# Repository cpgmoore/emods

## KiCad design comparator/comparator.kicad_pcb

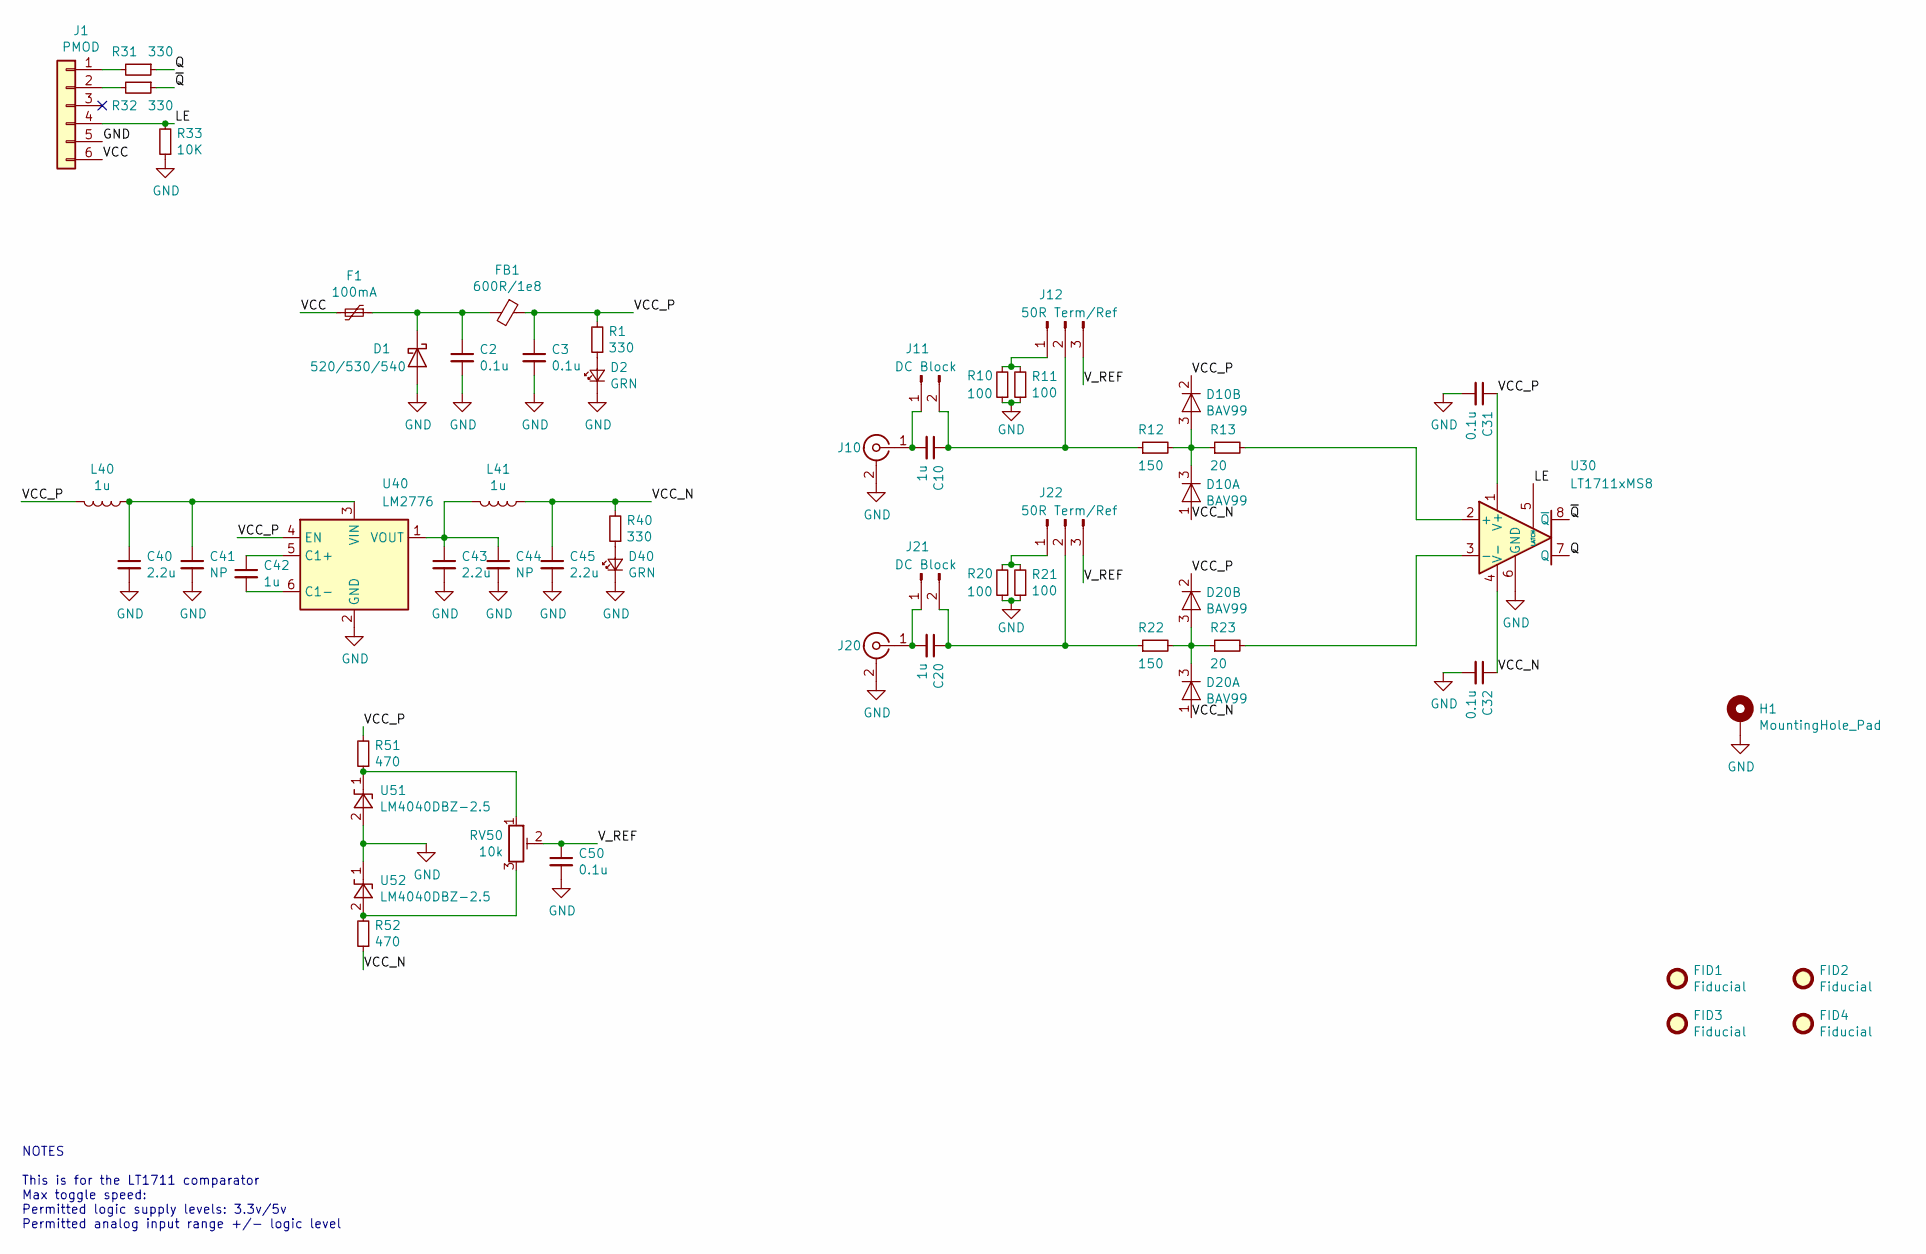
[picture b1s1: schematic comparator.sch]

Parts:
C2, C3, C31, C32, C50: 0.1u; C_0603_1608Metric
C10, C20, C42: 1u; C_0603_1608Metric
C40, C43, C45: 2.2u; C_0603_1608Metric
C41, C44: NP; C_0603_1608Metric
D1: 520/530/540; D_SOD-123
D2, D40: GRN; LED_0603_1608Metric
D10, D20: BAV99; SOT-23
F1: 100mA; Fuse_1206_3216Metric
FB1: 600R/1e8; L_0603_1608Metric
FID1, FID2, FID3, FID4: Fiducial; Fiducial_1mm_Mask2mm
H1: MountingHole_Pad; MountingHole_3.5mm_Pad_Via
J1: PMOD; PinHeader_1x06_P2.54mm_Vertical
J10, J20: SMA; SMA_Samtec_SMA-J-P-H-ST-EM1_EdgeMount
J11, J21: DC Block; PinHeader_1x02_P2.54mm_Vertical
J12, J22: 50R Term/Ref; PinHeader_1x03_P2.54mm_Vertical
L40, L41: 1u; L_0603_1608Metric
R1, R31, R32, R40: 330; R_0603_1608Metric
R10, R11, R20, R21: 100; R_0603_1608Metric
R12, R22: 150; R_0603_1608Metric
R13, R23: 20; R_0603_1608Metric
R33: 10K; R_0603_1608Metric
R51, R52: 470; R_0603_1608Metric
RV50: 10k; Potentiometer_Bourns_3299W_Vertical
U30: LT1711xMS8; MSOP-8_3x3mm_P0.65mm
U40: LM2776; SOT-23-6
U51, U52: LM4040DBZ-2.5; SOT-23

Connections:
/LE: J1.4, R33.2, U30.5 (LATCH)
/Q: R31.1, U30.7 (Q)
/VCC: F1.2, J1.6
/VCC_N: C32.1, C45.1, D10.1 (A), D20.1 (A), L41.1, R40.2, R52.1, U30.4 (V-)
/VCC_P: C3.1, C31.1, D10.2 (K), D20.2 (K), FB1.1, L40.2, R1.2, R51.2, U30.1 (V+), U40.4 (EN)
/V_REF: C50.1, J12.3, J22.3, RV50.2
/~Q: R32.1, U30.8 (~Q)
GND: C2.2, C3.2, C31.2, C32.2, C40.2, C41.2, C43.2, C44.2, C45.2, C50.2, D1.2 (A), D2.1 (K), D40.1 (K), H1.1, J1.5, J10.2 (Ext), J20.2 (Ext), R10.1, R11.1, R20.1, R21.1, R33.1, U30.6 (GND), U40.2 (GND), U51.2 (A), U52.1 (K)
unnamed: C2.1, D1.1 (K), F1.1, FB1.2
unnamed: C10.1, J11.2, J12.2, R12.1
unnamed: C10.2, J10.1 (In), J11.1
unnamed: C20.1, J21.2, J22.2, R22.1
unnamed: C20.2, J20.1 (In), J21.1
unnamed: C40.1, C41.1, L40.1, U40.3 (VIN)
unnamed: C42.1, U40.5 (C1+)
unnamed: C42.2, U40.6 (C1-)
unnamed: C43.1, C44.1, L41.2, U40.1 (VOUT)
unnamed: D2.2 (A), R1.1
unnamed: D10.3 (K), R12.2, R13.1
unnamed: D20.3 (K), R22.2, R23.1
unnamed: D40.2 (A), R40.1
unnamed: J1.1, R31.2
unnamed: J1.2, R32.2
unnamed: J12.1, R10.2, R11.2
unnamed: J22.1, R20.2, R21.2
unnamed: R13.2, U30.2 (+)
unnamed: R23.2, U30.3 (-)
unnamed: R51.1, RV50.1, U51.1 (K)
unnamed: R52.2, RV50.3, U52.2 (A)

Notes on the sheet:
NOTES This is for the LT1711 comparator Max toggle speed: Permitted logic supply levels: 3.3v/5v Permitted analog input range +/- logic level

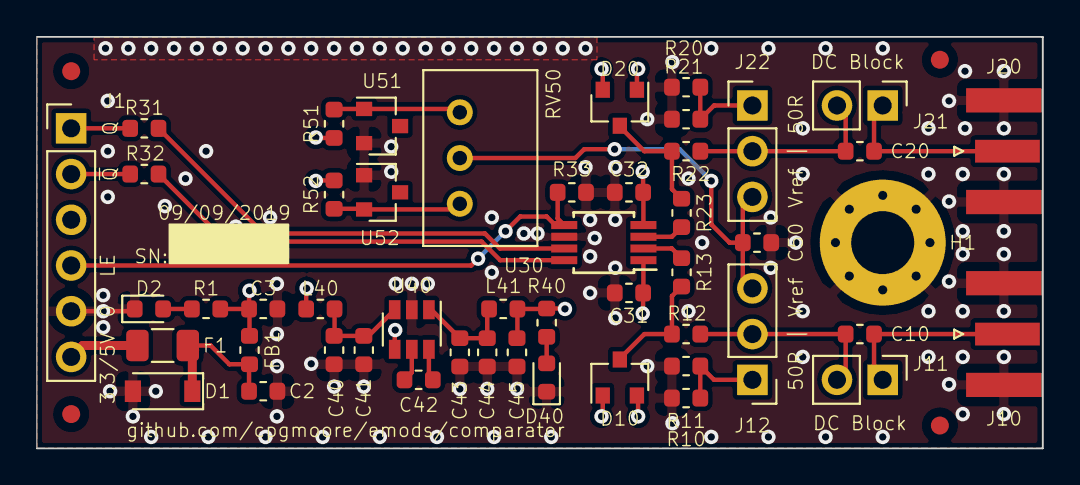
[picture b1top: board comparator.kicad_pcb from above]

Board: 4 copper layers, 55.9 x 22.9 mm, 54 parts (0 on the bottom side), 29 nets.

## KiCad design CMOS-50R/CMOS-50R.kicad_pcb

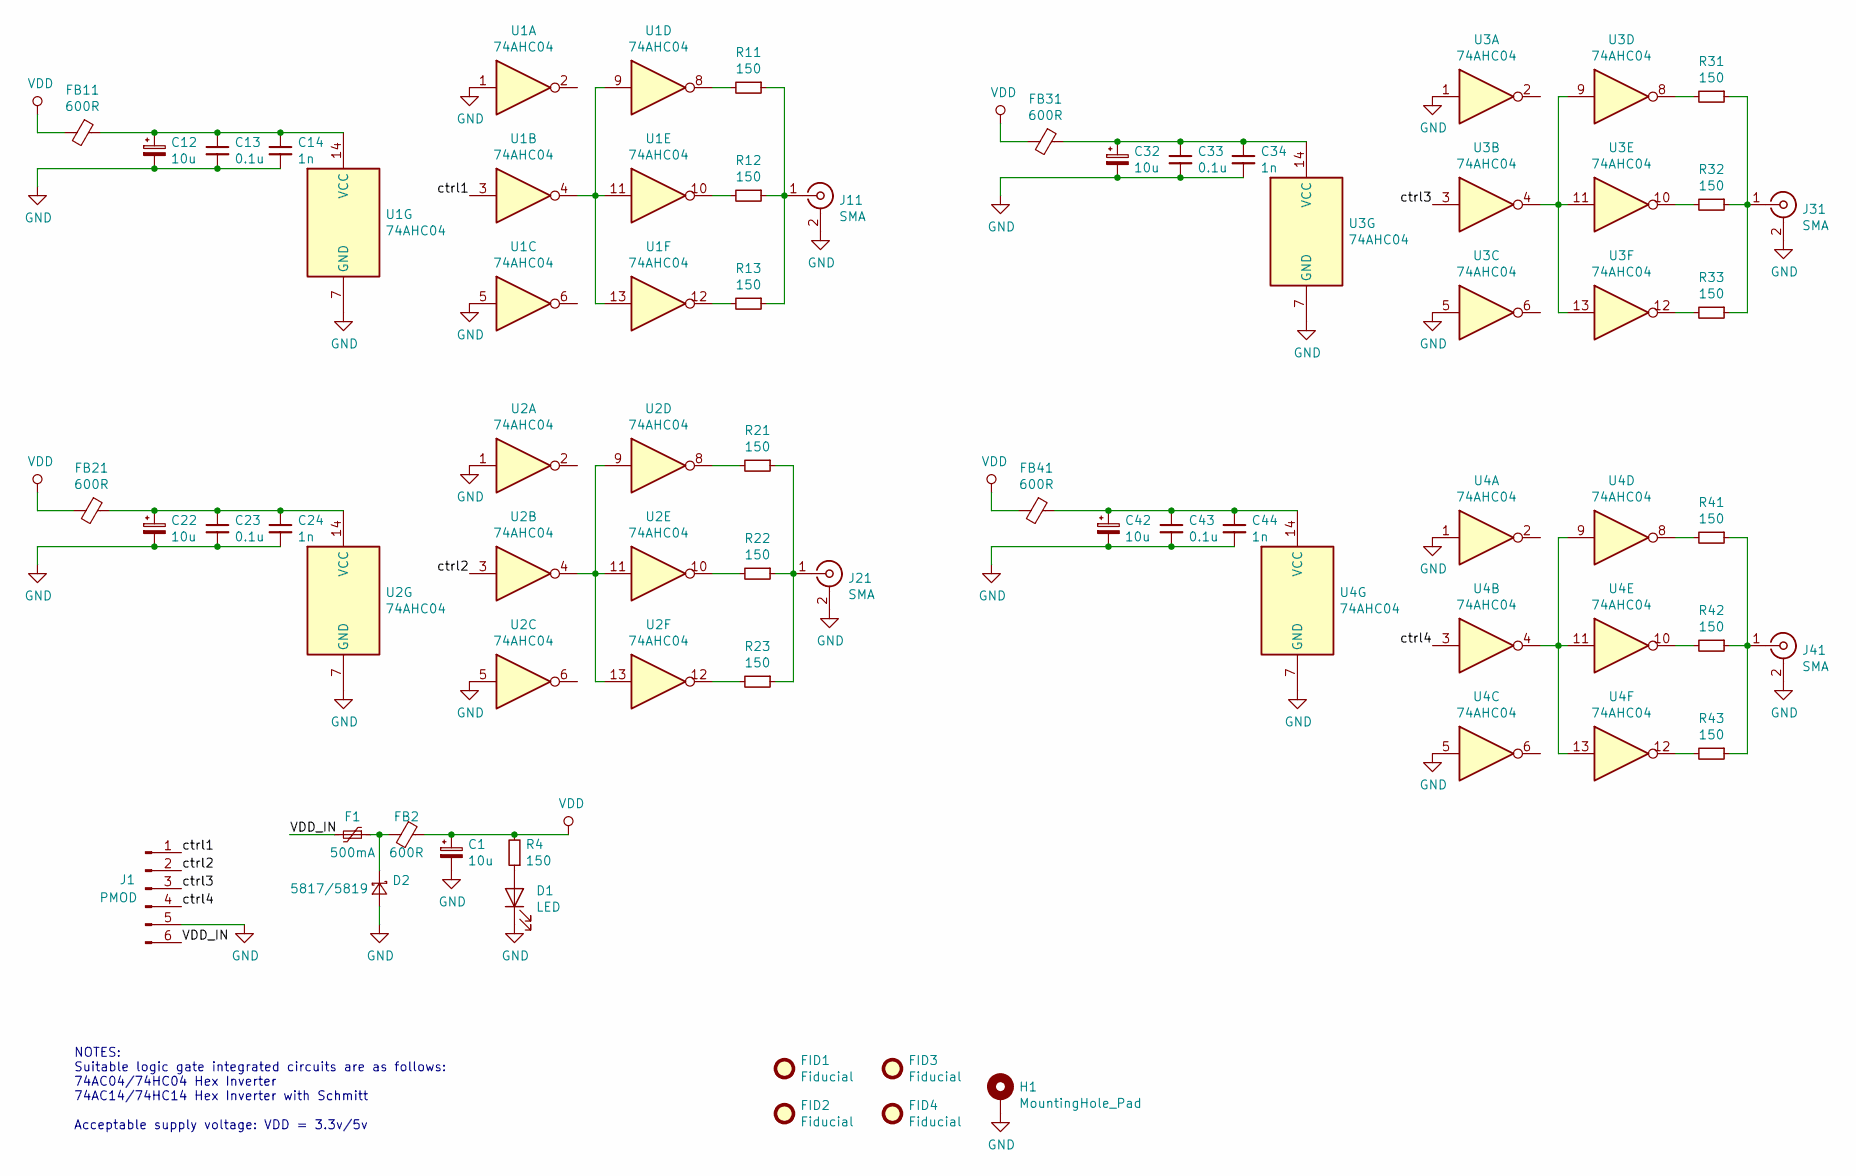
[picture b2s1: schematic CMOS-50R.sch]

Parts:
C1, C12, C22, C32, C42: 10u; CP_EIA-2012-12_Kemet-R
C13, C23, C33, C43: 0.1u; C_0603_1608Metric
C14, C24, C34, C44: 1n; C_0603_1608Metric
D1: LED; LED_0805_2012Metric
D2: 5817/5819; D_SOD-123
F1: 500mA; Fuse_1206_3216Metric
FB2, FB11, FB21, FB31, FB41: 600R; L_0603_1608Metric
FID1, FID2, FID3, FID4: Fiducial; Fiducial_1mm_Mask2mm
H1: MountingHole_Pad; MountingHole_3.5mm_Pad_Via
J1: PMOD; PinHeader_1x06_P2.54mm_Vertical
J11, J21, J31, J41: SMA; SMA_Amphenol_132134-11_Vertical
R4, R11, R12, R13, R21, R22, R23, R31, R32, R33, R41, R42, R43: 150; R_0805_2012Metric
U1, U2, U3, U4: 74AHC04; SOIC-14_3.9x8.7mm_P1.27mm

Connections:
/VDD_IN: F1.2, J1.6
/ctrl1: J1.1, U1.3
/ctrl2: J1.2, U2.3
/ctrl3: J1.3, U3.3
/ctrl4: J1.4, U4.3
GND: C1.2, C12.2, C13.2, C14.2, C22.2, C23.2, C24.2, C32.2, C33.2, C34.2, C42.2, C43.2, C44.2, D1.1 (K), D2.2 (A), H1.1, J1.5, J11.2 (Ext), J21.2 (Ext), J31.2 (Ext), J41.2 (Ext), U1.1, U1.5, U1.7 (GND), U2.1, U2.5, U2.7 (GND), U3.1, U3.5, U3.7 (GND), U4.1, U4.5, U4.7 (GND)
unnamed: C12.1, C13.1, C14.1, FB11.1, U1.14 (VCC)
unnamed: C22.1, C23.1, C24.1, FB21.1, U2.14 (VCC)
unnamed: C32.1, C33.1, C34.1, FB31.1, U3.14 (VCC)
unnamed: C42.1, C43.1, C44.1, FB41.1, U4.14 (VCC)
unnamed: D1.2 (A), R4.1
unnamed: D2.1 (K), F1.1, FB2.2
unnamed: J11.1 (In), R11.1, R12.1, R13.1
unnamed: J21.1 (In), R21.1, R22.1, R23.1
unnamed: J31.1 (In), R31.1, R32.1, R33.1
unnamed: J41.1 (In), R41.1, R42.1, R43.1
unnamed: R11.2, U1.8
unnamed: R12.2, U1.10
unnamed: R13.2, U1.12
unnamed: R21.2, U2.8
unnamed: R22.2, U2.10
unnamed: R23.2, U2.12
unnamed: R31.2, U3.8
unnamed: R32.2, U3.10
unnamed: R33.2, U3.12
unnamed: R41.2, U4.8
unnamed: R42.2, U4.10
unnamed: R43.2, U4.12
unnamed: U1.4, U1.9, U1.11, U1.13
unnamed: U2.4, U2.9, U2.11, U2.13
unnamed: U3.4, U3.9, U3.11, U3.13
unnamed: U4.4, U4.9, U4.11, U4.13
VDD: C1.1, FB2.1, FB11.2, FB21.2, FB31.2, FB41.2, R4.2

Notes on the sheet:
NOTES: Suitable logic gate integrated circuits are as follows: 74AC04/74HC04 Hex Inverter 74AC14/74HC14 Hex Inverter with Schmitt Acceptable supply voltage: VDD = 3.3v/5v

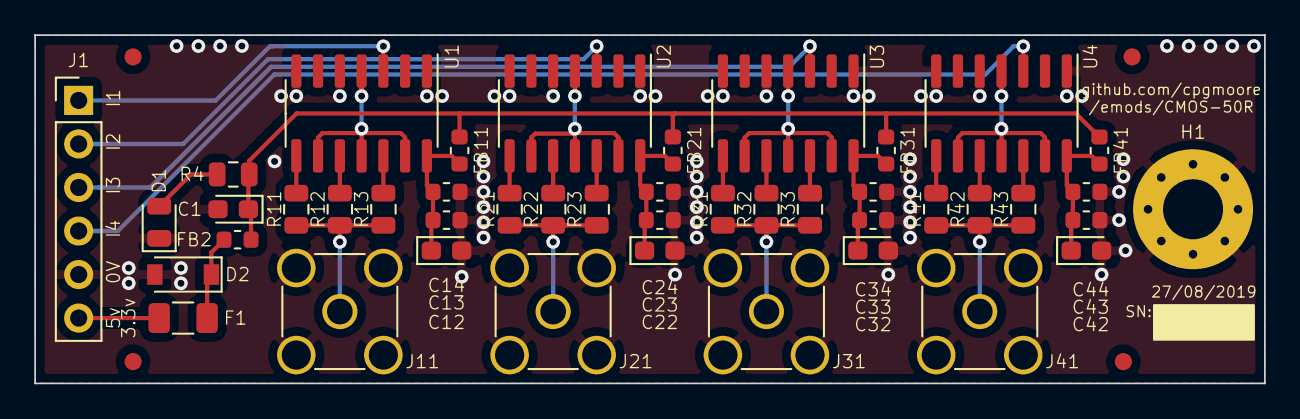
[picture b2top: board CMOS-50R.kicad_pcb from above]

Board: 2 copper layers, 71.8 x 20.3 mm, 48 parts (0 on the bottom side), 33 nets.

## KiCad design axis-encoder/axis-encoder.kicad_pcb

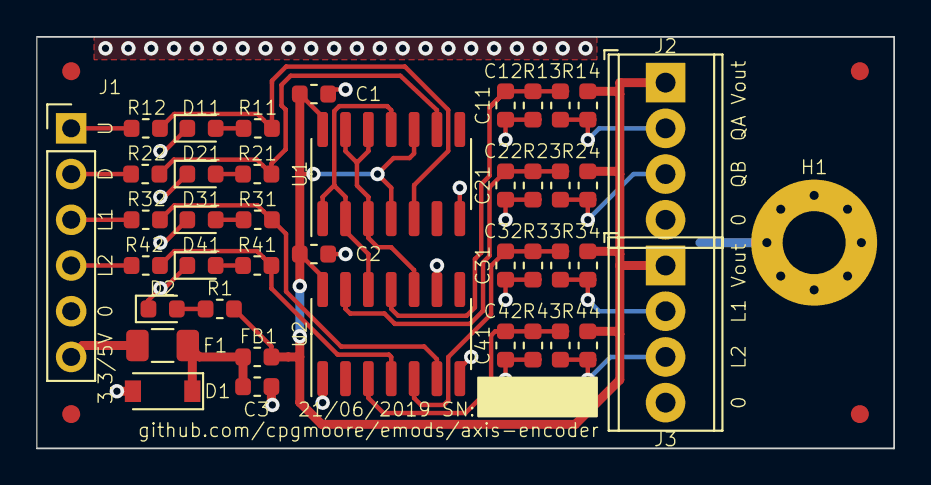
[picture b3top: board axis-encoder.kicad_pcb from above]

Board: 2 copper layers, 47.6 x 22.9 mm, 46 parts (0 on the bottom side), 27 nets.

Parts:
C1, C2, C3: 0.1u; C_0603_1608Metric
C11, C21, C31, C41: 1n; C_0603_1608Metric
C12, C22, C32, C42: NP; C_0603_1608Metric
D1: 520/530/540; D_SOD-123
D2: GRN; LED_0603_1608Metric
D11, D21, D31, D41: RED; LED_0603_1608Metric
F1: 100mA; Fuse_1206_3216Metric
FB1: 600R/1e8; L_0603_1608Metric
FID1, FID2, FID3, FID4: Fiducial; Fiducial_1mm_Mask2mm
H1: MountingHole_Pad; MountingHole_3.5mm_Pad_Via
J1: PMOD; PinHeader_1x06_P2.54mm_Vertical
J2: Encoder; TerminalBlock_Phoenix_MPT-0,5-4-2.54_1x04_P2.54mm_Horizontal
J3: Limits; TerminalBlock_Phoenix_MPT-0,5-4-2.54_1x04_P2.54mm_Horizontal
R1, R11, R21, R31, R41: 330; R_0603_1608Metric
R12, R14, R22, R24, R32, R34, R42, R44: 1k; R_0603_1608Metric
R13, R23, R33, R43: 10k; R_0603_1608Metric
U1: 74xx74; SOIC-14_3.9x8.7mm_P1.27mm
U2: 74xx14; SOIC-14_3.9x8.7mm_P1.27mm

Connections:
/LIM_1: J3.2, R33.1, R34.1
/LIM_2: J3.3, R43.1, R44.1
/L_1: J1.3, R32.2
/L_2: J1.4, R42.2
/QUAD_A: J2.2, R13.1, R14.1
/QUAD_B: J2.3, R23.1, R24.1
/Q_DN: J1.2, R22.2
/Q_UP: J1.1, R12.2
/VCC: F1.2, J1.6
GND: C1.2, C2.2, C3.2, C11.2, C12.2, C21.2, C22.2, C31.2, C32.2, C41.2, C42.2, D1.2, D2.1, D11.1, D21.1, D31.1, D41.1, H1.1, J1.5, J2.4, J3.4, U1.7, U2.1, U2.7, U2.9
unnamed: C3.1, D1.1, F1.1, FB1.2
unnamed: C11.1, C12.1, R13.2, U2.11
unnamed: C21.1, C22.1, R23.2, U2.13
unnamed: C31.1, C32.1, R33.2, U2.5
unnamed: C41.1, C42.1, R43.2, U2.3
unnamed: D2.2, R1.1
unnamed: D11.2, R11.1
unnamed: D21.2, R21.1
unnamed: D31.2, R31.1
unnamed: D41.2, R41.1
unnamed: R11.2, R12.1, U1.5
unnamed: R21.2, R22.1, U1.9
unnamed: R31.2, R32.1, U2.6
unnamed: R41.2, R42.1, U2.4
unnamed: U1.1, U1.2, U1.11, U2.12
unnamed: U1.3, U1.12, U1.13, U2.10
Vcc: C1.1, C2.1, FB1.1, J2.1, J3.1, R1.2, R14.2, R24.2, R34.2, R44.2, U1.4, U1.10, U1.14, U2.14

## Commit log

2019-08-19 good morning
2019-08-22 updated project name
2019-08-27 updated polarity protect and filter caps, layout progress
2019-08-27 layout updates
2019-08-27 Added fiducials and mounting hole
2019-08-27 First full functional layout trace route
2019-08-27 added 3d render
2019-08-27 finished annotations
2019-08-27 Exported PDFs
2019-08-27 Exported gerbers for manufacture
2019-08-30 Powerplane rearranged
2019-08-30 Finalised layout of silkscreen and fab annotation
2019-08-30 Finished ground stitching vias
2019-09-06 Added gitignore
2019-09-09 exported 3d view
2019-09-09 Released Rev 09/09/19 first manufacture
2019-09-09 Removed irrelevant files left over from previous project as template
